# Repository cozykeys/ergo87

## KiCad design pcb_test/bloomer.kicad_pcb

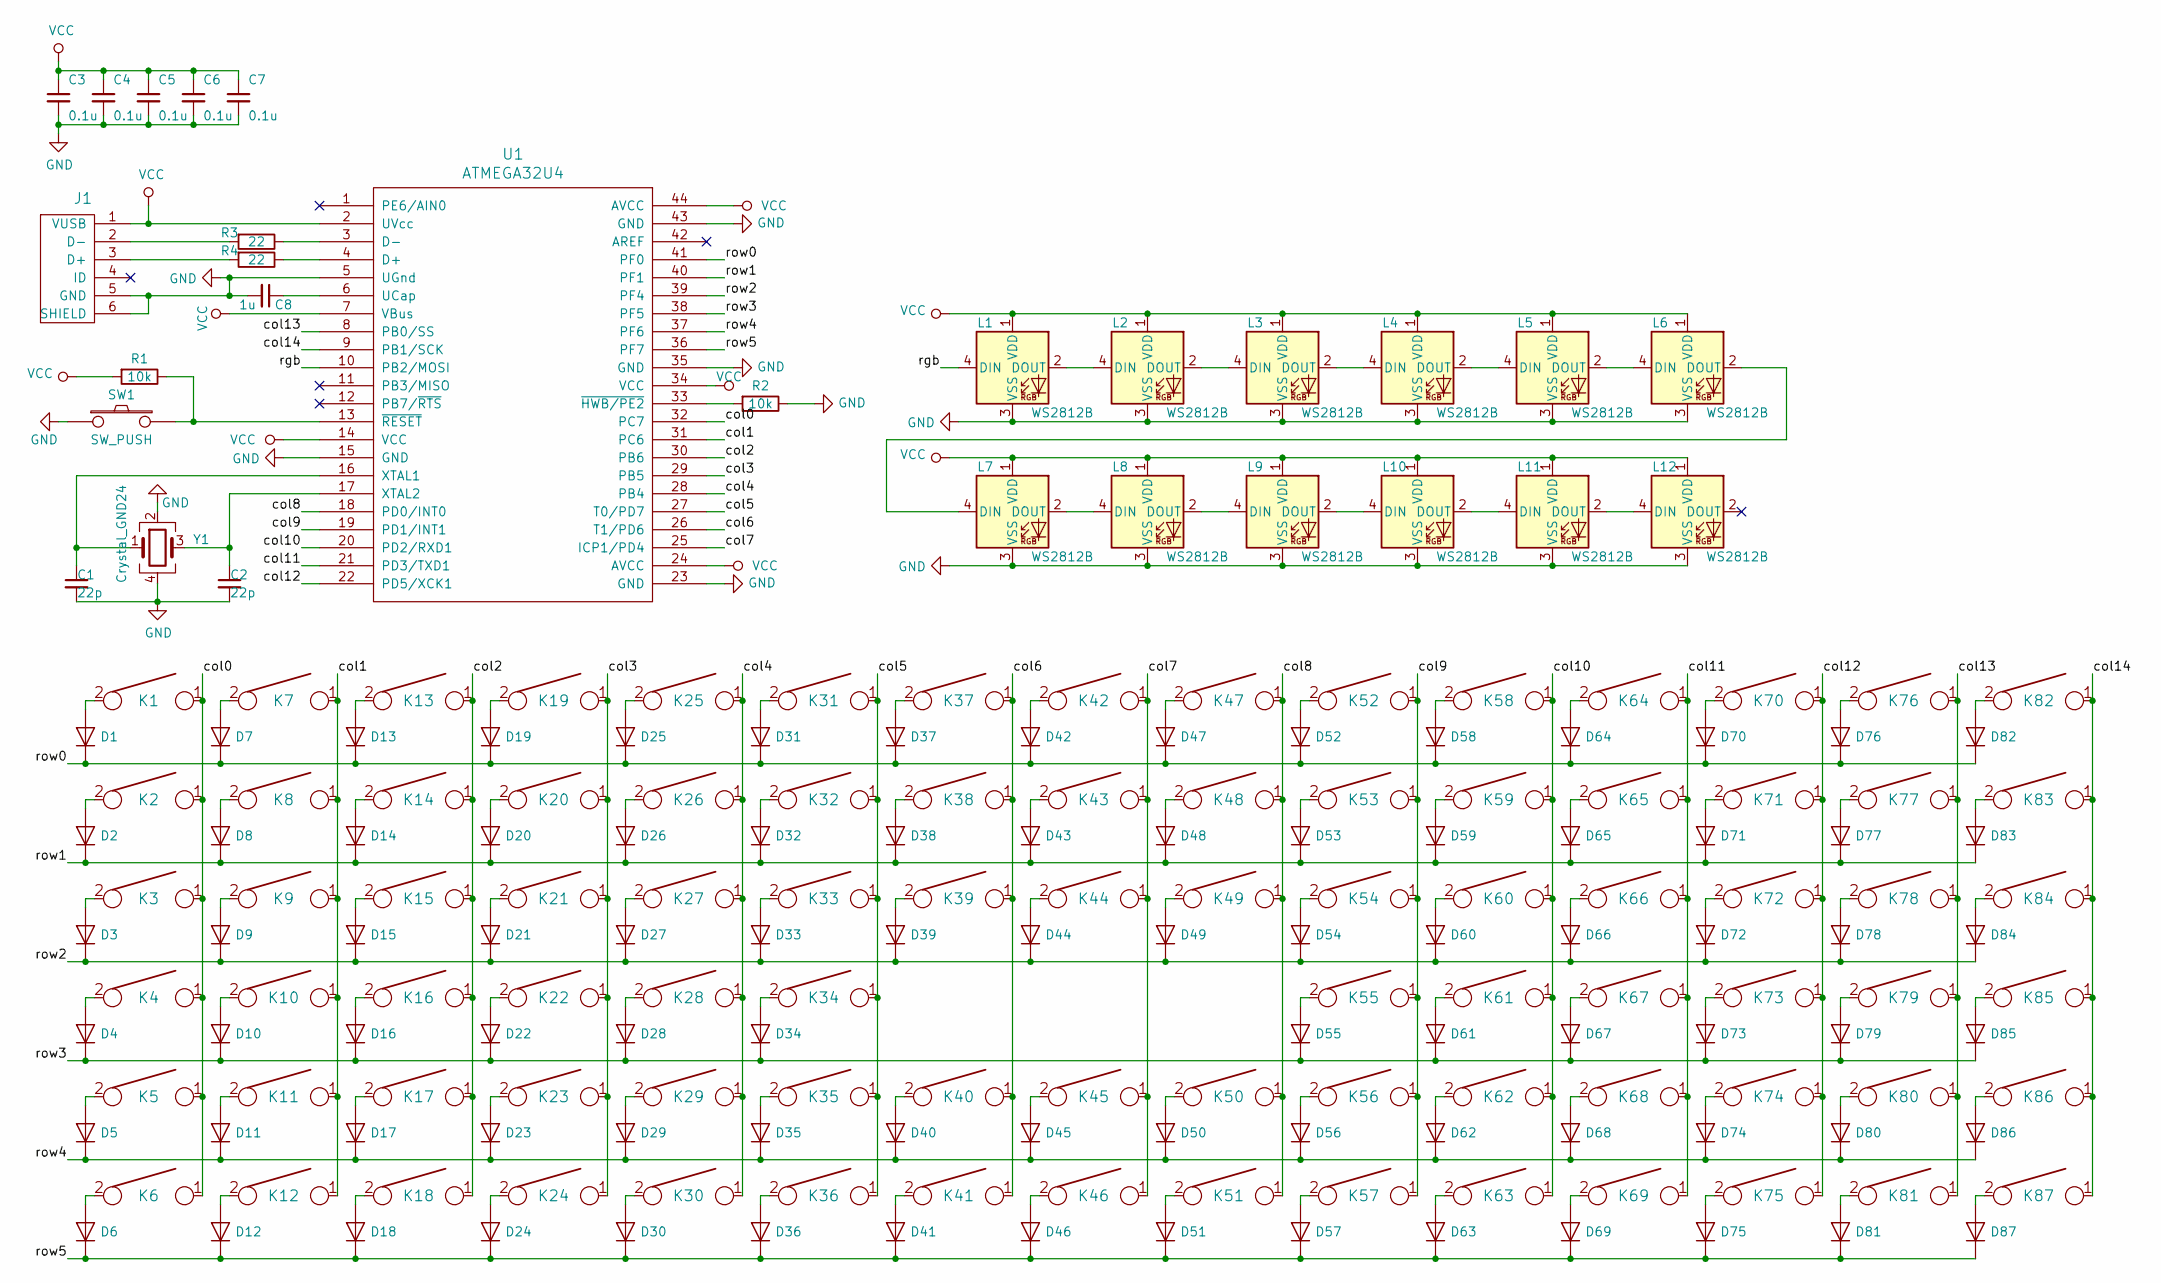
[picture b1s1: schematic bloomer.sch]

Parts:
C1, C2: 22p; C_0805_2012Metric_Pad1.15x1.40mm_HandSolder
C3, C4, C5, C6, C7: 0.1u; C_0805_2012Metric_Pad1.15x1.40mm_HandSolder
C8: 1u; C_0805_2012Metric_Pad1.15x1.40mm_HandSolder
D1, D2, D3, D4, D5, D6, D7, D8, D9, D10, D11, D12, D13, D14, D15, D16, D17, D18, D19, D20, D21, D22, D23, D24, D25, D26, D27, D28, D29, D30, D31, D32, D33, D34, D35, D36, D37, D38, D39, D40, D41, D42, D43, D44, D45, D46, D47, D48, D49, D50, D51, D52, D53, D54, D55, D56, D57, D58, D59, D60, D61, D62, D63, D64, D65, D66, D67, D68, D69, D70, D71, D72, D73, D74, D75, D76, D77, D78, D79, D80, D81, D82, D83, D84, D85, D86, D87: D; D_SOD123_axial
J1: USB_mini_micro_B; USB_miniB_hirose_5S8
K1, K2, K3, K4, K5, K6, K7, K8, K9, K10, K11, K12, K13, K14, K15, K16, K17, K18, K19, K20, K21, K22, K23, K24, K25, K26, K27, K28, K29, K30, K31, K32, K33, K34, K35, K36, K37, K38, K39, K40, K41, K42, K43, K44, K45, K46, K47, K48, K49, K50, K51, K52, K53, K54, K55, K56, K57, K58, K59, K60, K61, K62, K63, K64, K65, K66, K67, K68, K69, K70, K71, K72, K73, K74, K75, K76, K77, K78, K79, K80, K81, K82, K83, K84, K85, K86, K87: KEYSW; Mx_Alps_100
L1, L2, L3, L4, L5, L6, L7, L8, L9, L10, L11, L12: WS2812B; LED_WS2812B_PLCC4_5.0x5.0mm_P3.2mm
R1, R2: 10k; R_0805_2012Metric_Pad1.15x1.40mm_HandSolder
R3, R4: 22; R_0805_2012Metric_Pad1.15x1.40mm_HandSolder
SW1: SW_PUSH; SW_SPST_TL3342
U1: ATMEGA32U4; TQFP-44_10x10mm_P0.8mm
Y1: Crystal_GND24; Crystal_SMD_TXC_7M-4Pin_3.2x2.5mm_HandSoldering

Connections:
/col0: K1.1, K2.1, K3.1, K4.1, K5.1, K6.1, U1.32 (PC7)
/col1: K7.1, K8.1, K9.1, K10.1, K11.1, K12.1, U1.31 (PC6)
/col2: K13.1, K14.1, K15.1, K16.1, K17.1, K18.1, U1.30 (PB6)
/col3: K19.1, K20.1, K21.1, K22.1, K23.1, K24.1, U1.29 (PB5)
/col4: K25.1, K26.1, K27.1, K28.1, K29.1, K30.1, U1.28 (PB4)
/col5: K31.1, K32.1, K33.1, K34.1, K35.1, K36.1, U1.27 (T0/PD7)
/col6: K37.1, K38.1, K39.1, K40.1, K41.1, U1.26 (T1/PD6)
/col7: K42.1, K43.1, K44.1, K45.1, K46.1, U1.25 (ICP1/PD4)
/col8: K47.1, K48.1, K49.1, K50.1, K51.1, U1.18 (PD0/INT0)
/col9: K52.1, K53.1, K54.1, K55.1, K56.1, K57.1, U1.19 (PD1/INT1)
/col10: K58.1, K59.1, K60.1, K61.1, K62.1, K63.1, U1.20 (PD2/RXD1)
/col11: K64.1, K65.1, K66.1, K67.1, K68.1, K69.1, U1.21 (PD3/TXD1)
/col12: K70.1, K71.1, K72.1, K73.1, K74.1, K75.1, U1.22 (PD5/XCK1)
/col13: K76.1, K77.1, K78.1, K79.1, K80.1, K81.1, U1.8 (PB0/SS)
/col14: K82.1, K83.1, K84.1, K85.1, K86.1, K87.1, U1.9 (PB1/SCK)
/rgb: L1.4 (DIN), U1.10 (PB2/MOSI)
/row0: D1.1 (K), D7.1 (K), D13.1 (K), D19.1 (K), D25.1 (K), D31.1 (K), D37.1 (K), D42.1 (K), D47.1 (K), D52.1 (K), D58.1 (K), D64.1 (K), D70.1 (K), D76.1 (K), D82.1 (K), U1.41 (PF0)
/row1: D2.1 (K), D8.1 (K), D14.1 (K), D20.1 (K), D26.1 (K), D32.1 (K), D38.1 (K), D43.1 (K), D48.1 (K), D53.1 (K), D59.1 (K), D65.1 (K), D71.1 (K), D77.1 (K), D83.1 (K), U1.40 (PF1)
/row2: D3.1 (K), D9.1 (K), D15.1 (K), D21.1 (K), D27.1 (K), D33.1 (K), D39.1 (K), D44.1 (K), D49.1 (K), D54.1 (K), D60.1 (K), D66.1 (K), D72.1 (K), D78.1 (K), D84.1 (K), U1.39 (PF4)
/row3: D4.1 (K), D10.1 (K), D16.1 (K), D22.1 (K), D28.1 (K), D34.1 (K), D55.1 (K), D61.1 (K), D67.1 (K), D73.1 (K), D79.1 (K), D85.1 (K), U1.38 (PF5)
/row4: D5.1 (K), D11.1 (K), D17.1 (K), D23.1 (K), D29.1 (K), D35.1 (K), D40.1 (K), D45.1 (K), D50.1 (K), D56.1 (K), D62.1 (K), D68.1 (K), D74.1 (K), D80.1 (K), D86.1 (K), U1.37 (PF6)
/row5: D6.1 (K), D12.1 (K), D18.1 (K), D24.1 (K), D30.1 (K), D36.1 (K), D41.1 (K), D46.1 (K), D51.1 (K), D57.1 (K), D63.1 (K), D69.1 (K), D75.1 (K), D81.1 (K), D87.1 (K), U1.36 (PF7)
GND: C1.2, C2.2, C3.2, C4.2, C5.2, C6.2, C7.2, C8.2, J1.5 (GND), J1.6 (SHIELD), L1.3 (VSS), L2.3 (VSS), L3.3 (VSS), L4.3 (VSS), L5.3 (VSS), L6.3 (VSS), L7.3 (VSS), L8.3 (VSS), L9.3 (VSS), L10.3 (VSS), L11.3 (VSS), L12.3 (VSS), R2.1, SW1.1, U1.5 (UGnd), U1.15 (GND), U1.23 (GND), U1.35 (GND), U1.43 (GND), Y1.2, Y1.4
unnamed: C1.1, U1.16 (XTAL1), Y1.1
unnamed: C2.1, U1.17 (XTAL2), Y1.3
unnamed: C8.1, U1.6 (UCap)
unnamed: D1.2 (A), K1.2
unnamed: D2.2 (A), K2.2
unnamed: D3.2 (A), K3.2
unnamed: D4.2 (A), K4.2
unnamed: D5.2 (A), K5.2
unnamed: D6.2 (A), K6.2
unnamed: D7.2 (A), K7.2
unnamed: D8.2 (A), K8.2
unnamed: D9.2 (A), K9.2
unnamed: D10.2 (A), K10.2
unnamed: D11.2 (A), K11.2
unnamed: D12.2 (A), K12.2
unnamed: D13.2 (A), K13.2
unnamed: D14.2 (A), K14.2
unnamed: D15.2 (A), K15.2
unnamed: D16.2 (A), K16.2
unnamed: D17.2 (A), K17.2
unnamed: D18.2 (A), K18.2
unnamed: D19.2 (A), K19.2
unnamed: D20.2 (A), K20.2
unnamed: D21.2 (A), K21.2
unnamed: D22.2 (A), K22.2
unnamed: D23.2 (A), K23.2
unnamed: D24.2 (A), K24.2
unnamed: D25.2 (A), K25.2
unnamed: D26.2 (A), K26.2
unnamed: D27.2 (A), K27.2
unnamed: D28.2 (A), K28.2
unnamed: D29.2 (A), K29.2
unnamed: D30.2 (A), K30.2
unnamed: D31.2 (A), K31.2
unnamed: D32.2 (A), K32.2
unnamed: D33.2 (A), K33.2
unnamed: D34.2 (A), K34.2
unnamed: D35.2 (A), K35.2
unnamed: D36.2 (A), K36.2
unnamed: D37.2 (A), K37.2
unnamed: D38.2 (A), K38.2
unnamed: D39.2 (A), K39.2
unnamed: D40.2 (A), K40.2
unnamed: D41.2 (A), K41.2
unnamed: D42.2 (A), K42.2
unnamed: D43.2 (A), K43.2
unnamed: D44.2 (A), K44.2
unnamed: D45.2 (A), K45.2
unnamed: D46.2 (A), K46.2
unnamed: D47.2 (A), K47.2
unnamed: D48.2 (A), K48.2
unnamed: D49.2 (A), K49.2
unnamed: D50.2 (A), K50.2
unnamed: D51.2 (A), K51.2
unnamed: D52.2 (A), K52.2
unnamed: D53.2 (A), K53.2
unnamed: D54.2 (A), K54.2
unnamed: D55.2 (A), K55.2
unnamed: D56.2 (A), K56.2
unnamed: D57.2 (A), K57.2
unnamed: D58.2 (A), K58.2
unnamed: D59.2 (A), K59.2
unnamed: D60.2 (A), K60.2
unnamed: D61.2 (A), K61.2
unnamed: D62.2 (A), K62.2
unnamed: D63.2 (A), K63.2
unnamed: D64.2 (A), K64.2
unnamed: D65.2 (A), K65.2
unnamed: D66.2 (A), K66.2
unnamed: D67.2 (A), K67.2
unnamed: D68.2 (A), K68.2
unnamed: D69.2 (A), K69.2
unnamed: D70.2 (A), K70.2
unnamed: D71.2 (A), K71.2
unnamed: D72.2 (A), K72.2
unnamed: D73.2 (A), K73.2
unnamed: D74.2 (A), K74.2
unnamed: D75.2 (A), K75.2
unnamed: D76.2 (A), K76.2
unnamed: D77.2 (A), K77.2
unnamed: D78.2 (A), K78.2
unnamed: D79.2 (A), K79.2
unnamed: D80.2 (A), K80.2
unnamed: D81.2 (A), K81.2
unnamed: D82.2 (A), K82.2
unnamed: D83.2 (A), K83.2
unnamed: D84.2 (A), K84.2
unnamed: D85.2 (A), K85.2
unnamed: D86.2 (A), K86.2
unnamed: D87.2 (A), K87.2
unnamed: J1.2 (D-), R3.2
unnamed: J1.3 (D+), R4.2
unnamed: L1.2 (DOUT), L2.4 (DIN)
unnamed: L2.2 (DOUT), L3.4 (DIN)
unnamed: L3.2 (DOUT), L4.4 (DIN)
unnamed: L4.2 (DOUT), L5.4 (DIN)
unnamed: L5.2 (DOUT), L6.4 (DIN)
unnamed: L6.2 (DOUT), L7.4 (DIN)
unnamed: L7.2 (DOUT), L8.4 (DIN)
unnamed: L8.2 (DOUT), L9.4 (DIN)
unnamed: L10.2 (DOUT), L11.4 (DIN)
unnamed: L9.2 (DOUT), L10.4 (DIN)
unnamed: L11.2 (DOUT), L12.4 (DIN)
unnamed: R1.1, SW1.2, U1.13 (~RESET)
unnamed: R2.2, U1.33 (~HWB/PE2)
unnamed: R3.1, U1.3 (D-)
unnamed: R4.1, U1.4 (D+)
VCC: C3.1, C4.1, C5.1, C6.1, C7.1, J1.1 (VUSB), L1.1 (VDD), L2.1 (VDD), L3.1 (VDD), L4.1 (VDD), L5.1 (VDD), L6.1 (VDD), L7.1 (VDD), L8.1 (VDD), L9.1 (VDD), L10.1 (VDD), L11.1 (VDD), L12.1 (VDD), R1.2, U1.2 (UVcc), U1.7 (VBus), U1.14 (VCC), U1.24 (AVCC), U1.34 (VCC), U1.44 (AVCC)

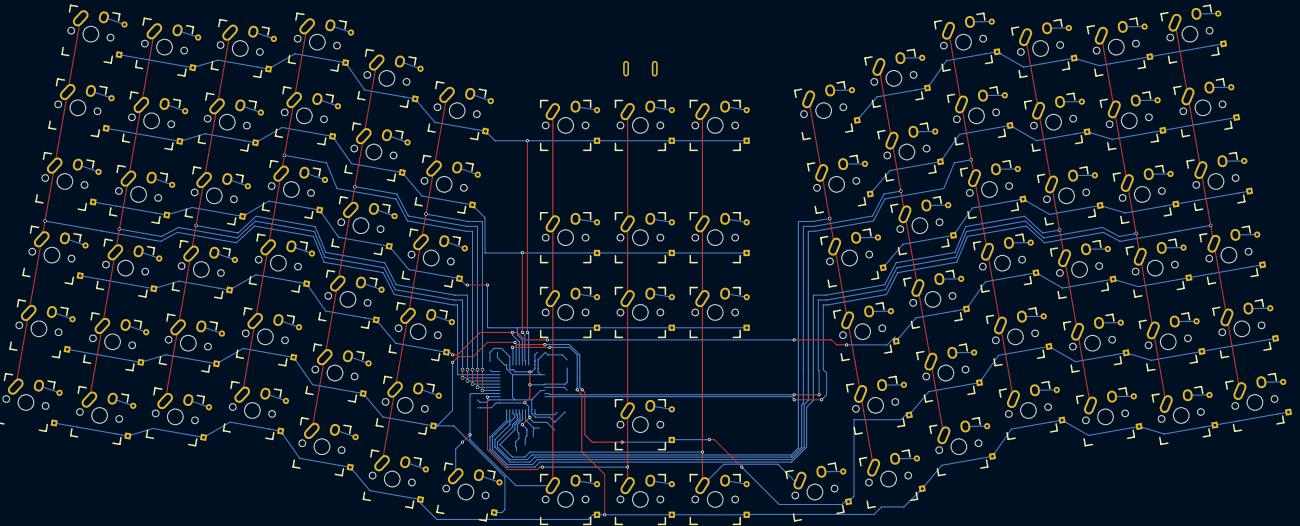
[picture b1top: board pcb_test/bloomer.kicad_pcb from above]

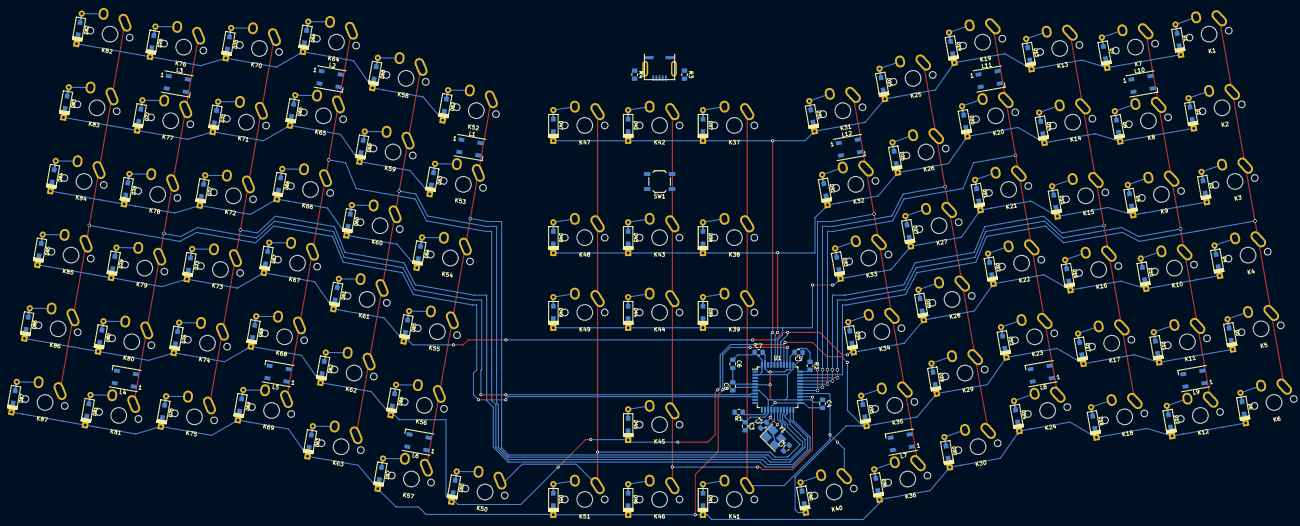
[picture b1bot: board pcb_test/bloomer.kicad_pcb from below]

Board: 2 copper layers, 202 parts (115 on the bottom side), 131 nets.

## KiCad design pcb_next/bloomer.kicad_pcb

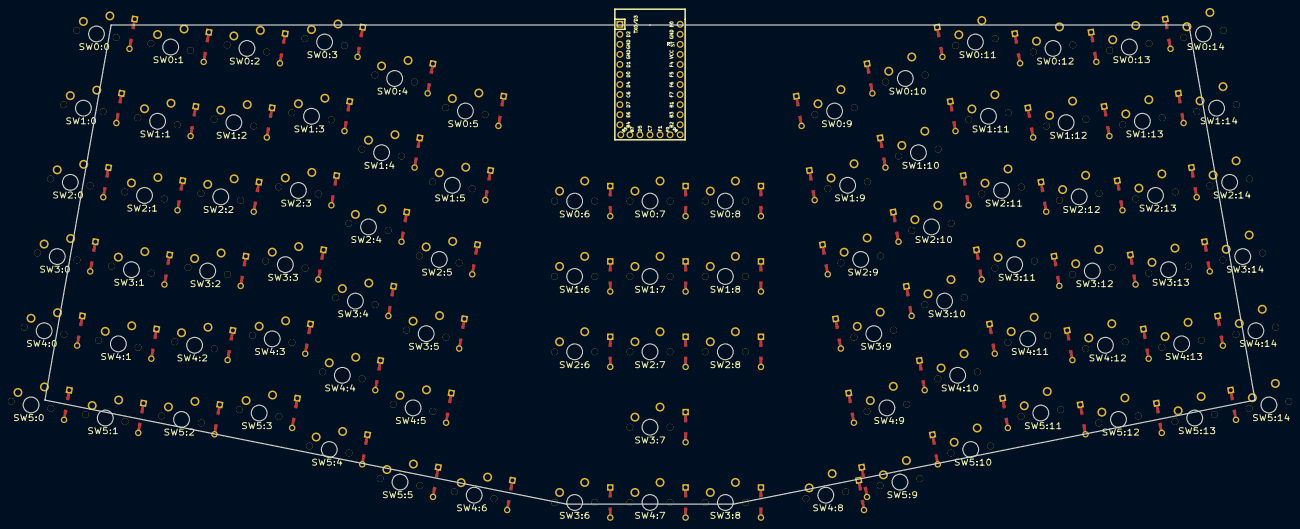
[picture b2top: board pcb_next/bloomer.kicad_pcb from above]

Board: 2 copper layers, 305.9 x 121.1 mm, 175 parts (0 on the bottom side), 108 nets, no tracks yet.

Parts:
D0:0, D0:1, D0:2, D0:3, D0:4, D0:5, D0:6, D0:7, D0:8, D0:9, D0:10, D0:11, D0:12, D0:13, D0:14, D1:0, D1:1, D1:2, D1:3, D1:4, D1:5, D1:6, D1:7, D1:8, D1:9, D1:10, D1:11, D1:12, D1:13, D1:14, D2:0, D2:1, D2:2, D2:3, D2:4, D2:5, D2:6, D2:7, D2:8, D2:9, D2:10, D2:11, D2:12, D2:13, D2:14, D3:0, D3:1, D3:2, D3:3, D3:4, D3:5, D3:6, D3:7, D3:8, D3:9, D3:10, D3:11, D3:12, D3:13, D3:14, D4:0, D4:1, D4:2, D4:3, D4:4, D4:5, D4:6, D4:7, D4:8, D4:9, D4:10, D4:11, D4:12, D4:13, D4:14, D5:0, D5:1, D5:2, D5:3, D5:4, D5:5, D5:9, D5:10, D5:11, D5:12, D5:13, D5:14: DIODE
SW0:0, SW0:1, SW0:2, SW0:3, SW0:4, SW0:5, SW0:6, SW0:7, SW0:8, SW0:9, SW0:10, SW0:11, SW0:12, SW0:13, SW0:14, SW1:0, SW1:1, SW1:2, SW1:3, SW1:4, SW1:5, SW1:6, SW1:7, SW1:8, SW1:9, SW1:10, SW1:11, SW1:12, SW1:13, SW1:14, SW2:0, SW2:1, SW2:2, SW2:3, SW2:4, SW2:5, SW2:6, SW2:7, SW2:8, SW2:9, SW2:10, SW2:11, SW2:12, SW2:13, SW2:14, SW3:0, SW3:1, SW3:2, SW3:3, SW3:4, SW3:5, SW3:6, SW3:7, SW3:8, SW3:9, SW3:10, SW3:11, SW3:12, SW3:13, SW3:14, SW4:0, SW4:1, SW4:2, SW4:3, SW4:4, SW4:5, SW4:6, SW4:7, SW4:8, SW4:9, SW4:10, SW4:11, SW4:12, SW4:13, SW4:14, SW5:0, SW5:1, SW5:2, SW5:3, SW5:4, SW5:5, SW5:9, SW5:10, SW5:11, SW5:12, SW5:13, SW5:14: MX
U1: Elite-C

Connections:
N-col-0: SW0:0.2, SW1:0.2, SW2:0.2, SW3:0.2, SW4:0.2, SW5:0.2
N-col-1: SW0:1.2, SW1:1.2, SW2:1.2, SW3:1.2, SW4:1.2, SW5:1.2
N-col-2: SW0:2.2, SW1:2.2, SW2:2.2, SW3:2.2, SW4:2.2, SW5:2.2
N-col-3: SW0:3.2, SW1:3.2, SW2:3.2, SW3:3.2, SW4:3.2, SW5:3.2
N-col-4: SW0:4.2, SW1:4.2, SW2:4.2, SW3:4.2, SW4:4.2, SW5:4.2
N-col-5: SW0:5.2, SW1:5.2, SW2:5.2, SW3:5.2, SW4:5.2, SW5:5.2
N-col-6: SW0:6.2, SW1:6.2, SW2:6.2, SW3:6.2, SW4:6.2
N-col-7: SW0:7.2, SW1:7.2, SW2:7.2, SW3:7.2, SW4:7.2
N-col-8: SW0:8.2, SW1:8.2, SW2:8.2, SW3:8.2, SW4:8.2
N-col-9: SW0:9.2, SW1:9.2, SW2:9.2, SW3:9.2, SW4:9.2, SW5:9.2
N-col-10: SW0:10.2, SW1:10.2, SW2:10.2, SW3:10.2, SW4:10.2, SW5:10.2
N-col-11: SW0:11.2, SW1:11.2, SW2:11.2, SW3:11.2, SW4:11.2, SW5:11.2
N-col-12: SW0:12.2, SW1:12.2, SW2:12.2, SW3:12.2, SW4:12.2, SW5:12.2
N-col-13: SW0:13.2, SW1:13.2, SW2:13.2, SW3:13.2, SW4:13.2, SW5:13.2
N-col-14: SW0:14.2, SW1:14.2, SW2:14.2, SW3:14.2, SW4:14.2, SW5:14.2
N-diode-0-0: D0:0.2, SW0:0.1
N-diode-0-1: D0:1.2, SW0:1.1
N-diode-0-2: D0:2.2, SW0:2.1
N-diode-0-3: D0:3.2, SW0:3.1
N-diode-0-4: D0:4.2, SW0:4.1
N-diode-0-5: D0:5.2, SW0:5.1
N-diode-0-6: D0:6.2, SW0:6.1
N-diode-0-7: D0:7.2, SW0:7.1
N-diode-0-8: D0:8.2, SW0:8.1
N-diode-0-9: D0:9.2, SW0:9.1
N-diode-0-10: D0:10.2, SW0:10.1
N-diode-0-11: D0:11.2, SW0:11.1
N-diode-0-12: D0:12.2, SW0:12.1
N-diode-0-13: D0:13.2, SW0:13.1
N-diode-0-14: D0:14.2, SW0:14.1
N-diode-1-0: D1:0.2, SW1:0.1
N-diode-1-1: D1:1.2, SW1:1.1
N-diode-1-2: D1:2.2, SW1:2.1
N-diode-1-3: D1:3.2, SW1:3.1
N-diode-1-4: D1:4.2, SW1:4.1
N-diode-1-5: D1:5.2, SW1:5.1
N-diode-1-6: D1:6.2, SW1:6.1
N-diode-1-7: D1:7.2, SW1:7.1
N-diode-1-8: D1:8.2, SW1:8.1
N-diode-1-9: D1:9.2, SW1:9.1
N-diode-1-10: D1:10.2, SW1:10.1
N-diode-1-11: D1:11.2, SW1:11.1
N-diode-1-12: D1:12.2, SW1:12.1
N-diode-1-13: D1:13.2, SW1:13.1
N-diode-1-14: D1:14.2, SW1:14.1
N-diode-2-0: D2:0.2, SW2:0.1
N-diode-2-1: D2:1.2, SW2:1.1
N-diode-2-2: D2:2.2, SW2:2.1
N-diode-2-3: D2:3.2, SW2:3.1
N-diode-2-4: D2:4.2, SW2:4.1
N-diode-2-5: D2:5.2, SW2:5.1
N-diode-2-6: D2:6.2, SW2:6.1
N-diode-2-7: D2:7.2, SW2:7.1
N-diode-2-8: D2:8.2, SW2:8.1
N-diode-2-9: D2:9.2, SW2:9.1
N-diode-2-10: D2:10.2, SW2:10.1
N-diode-2-11: D2:11.2, SW2:11.1
N-diode-2-12: D2:12.2, SW2:12.1
N-diode-2-13: D2:13.2, SW2:13.1
N-diode-2-14: D2:14.2, SW2:14.1
N-diode-3-0: D3:0.2, SW3:0.1
N-diode-3-1: D3:1.2, SW3:1.1
N-diode-3-2: D3:2.2, SW3:2.1
N-diode-3-3: D3:3.2, SW3:3.1
N-diode-3-4: D3:4.2, SW3:4.1
N-diode-3-5: D3:5.2, SW3:5.1
N-diode-3-6: D3:6.2, SW3:6.1
N-diode-3-7: D3:7.2, SW3:7.1
N-diode-3-8: D3:8.2, SW3:8.1
N-diode-3-9: D3:9.2, SW3:9.1
N-diode-3-10: D3:10.2, SW3:10.1
N-diode-3-11: D3:11.2, SW3:11.1
N-diode-3-12: D3:12.2, SW3:12.1
N-diode-3-13: D3:13.2, SW3:13.1
N-diode-3-14: D3:14.2, SW3:14.1
N-diode-4-0: D4:0.2, SW4:0.1
N-diode-4-1: D4:1.2, SW4:1.1
N-diode-4-2: D4:2.2, SW4:2.1
N-diode-4-3: D4:3.2, SW4:3.1
N-diode-4-4: D4:4.2, SW4:4.1
N-diode-4-5: D4:5.2, SW4:5.1
N-diode-4-6: D4:6.2, SW4:6.1
N-diode-4-7: D4:7.2, SW4:7.1
N-diode-4-8: D4:8.2, SW4:8.1
N-diode-4-9: D4:9.2, SW4:9.1
N-diode-4-10: D4:10.2, SW4:10.1
N-diode-4-11: D4:11.2, SW4:11.1
N-diode-4-12: D4:12.2, SW4:12.1
N-diode-4-13: D4:13.2, SW4:13.1
N-diode-4-14: D4:14.2, SW4:14.1
N-diode-5-0: D5:0.2, SW5:0.1
N-diode-5-1: D5:1.2, SW5:1.1
N-diode-5-2: D5:2.2, SW5:2.1
N-diode-5-3: D5:3.2, SW5:3.1
N-diode-5-4: D5:4.2, SW5:4.1
N-diode-5-5: D5:5.2, SW5:5.1
N-diode-5-9: D5:9.2, SW5:9.1
N-diode-5-10: D5:10.2, SW5:10.1
N-diode-5-11: D5:11.2, SW5:11.1
N-diode-5-12: D5:12.2, SW5:12.1
N-diode-5-13: D5:13.2, SW5:13.1
N-diode-5-14: D5:14.2, SW5:14.1
N-row-0: D0:0.1, D0:1.1, D0:2.1, D0:3.1, D0:4.1, D0:5.1, D0:6.1, D0:7.1, D0:8.1, D0:9.1, D0:10.1, D0:11.1, D0:12.1, D0:13.1, D0:14.1
N-row-1: D1:0.1, D1:1.1, D1:2.1, D1:3.1, D1:4.1, D1:5.1, D1:6.1, D1:7.1, D1:8.1, D1:9.1, D1:10.1, D1:11.1, D1:12.1, D1:13.1, D1:14.1
N-row-2: D2:0.1, D2:1.1, D2:2.1, D2:3.1, D2:4.1, D2:5.1, D2:6.1, D2:7.1, D2:8.1, D2:9.1, D2:10.1, D2:11.1, D2:12.1, D2:13.1, D2:14.1
N-row-3: D3:0.1, D3:1.1, D3:2.1, D3:3.1, D3:4.1, D3:5.1, D3:6.1, D3:7.1, D3:8.1, D3:9.1, D3:10.1, D3:11.1, D3:12.1, D3:13.1, D3:14.1
N-row-4: D4:0.1, D4:1.1, D4:2.1, D4:3.1, D4:4.1, D4:5.1, D4:6.1, D4:7.1, D4:8.1, D4:9.1, D4:10.1, D4:11.1, D4:12.1, D4:13.1, D4:14.1
N-row-5: D5:0.1, D5:1.1, D5:2.1, D5:3.1, D5:4.1, D5:5.1, D5:9.1, D5:10.1, D5:11.1, D5:12.1, D5:13.1, D5:14.1
